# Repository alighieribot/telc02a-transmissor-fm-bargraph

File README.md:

# Sistema de Transmissao FM VHF, Recepcao SDR e Indicador de Nivel Bargraph — TELC02A UNIFEI

Repositorio de engenharia, automacao de projeto eletronico, memorial de calculos e documentacao de bancada do sistema de transmissao em frequencia modulada e monitoramento visual de envolvente de audio desenvolvido para a disciplina **TELC02A — Telecomunicacoes II** da **Universidade Federal de Itajuba**.

---

## Identificacao Academica

| Campo | Informacao |
|---|---|
| **Instituicao** | Universidade Federal de Itajuba — UNIFEI |
| **Disciplina** | TELC02A — Telecomunicacoes II |
| **Docentes Responsaveis** | Prof. Dr. Danilo Henrique Spadoti e Prof. Dr. Mateus Augusto Faustino Chaib Junqueira |
| **Docentes e Tecnicos Colaboradores** | Prof. Dr. Decio Renno de Mendonca, Prof. Dr. Luciano Bertini e Tecnico Anderson — LPCI e LabTel |
| **Integrante 1** | Leonardo Mendonca Costa — Matricula 2024001025 |
| **Integrante 2** | Matheus Martins Venga — Matricula 2024005285 |
| **Integrante 3** | Pedro Henrique Dos Santos Barbosa — Matricula 2022013760 |
| **Integrante 4** | Pedro Henrique Oliveira Francisco — Matricula 2022003245 |
| **Relatorio Entregue** | [Relatorio Telecomunicacoes II.pdf](Relat%C3%B3rio%20Telecomunica%C3%A7%C3%B5es%20II.pdf) |

---

## Sumario

1. [Arquitetura do Sistema e Fluxo de Sinal](#1-arquitetura-do-sistema-e-fluxo-de-sinal)
2. [Fundamentacao Teorica](#2-fundamentacao-teorica)
3. [Adaptacoes de Topologia e Projeto de Esquematicos no KiCad 9.0](#3-adaptacoes-de-topologia-e-projeto-de-esquematicos-no-kicad-90)
4. [Especificacoes e Lista de Materiais](#4-especificacoes-e-lista-de-materiais)
5. [Memorial de Calculos de Engenharia](#5-memorial-de-calculos-de-engenharia)
6. [Projeto de Layout da PCB, Geometria Trapezoidal e Validacao ERC/DRC](#6-projeto-de-layout-da-pcb-geometria-trapezoidal-e-validacao-ercdrc)
7. [Processo de Fabricacao Fisica, Corrosao e Montagem das Placas](#7-processo-de-fabricacao-fisica-corrosao-e-montagem-das-placas)
8. [Ensaios de Bancada, Diagnostico de Falhas e Instrumentacao RF](#8-ensaios-de-bancada-diagnostico-de-falhas-e-instrumentacao-rf)
9. [Localizacao Diferencial da Portadora e Demodulacao WFM via RTL-SDR e SDR# Studio](#9-localizacao-diferencial-da-portadora-e-demodulacao-wfm-via-rtl-sdr-e-sdr-studio)
10. [Estrutura do Repositorio e Automacao via Scripts e Testes](#10-estrutura-do-repositorio-e-automacao-via-scripts-e-testes)
11. [Referencias Tecnicas](#11-referencias-tecnicas)

---

## 1. Arquitetura do Sistema e Fluxo de Sinal

O projeto compreende uma cadeia completa de comunicacao analogica em VHF dividida em tres subsistemas interconectados:

1. **Subsistema A — Transmissor FM VHF (`kicad/transmissor/`):** Oscilador Colpitts de estagio unico em configuracao de base comum alimentado por celula de ions de litio 18650 de $3{,}7\ \text{V}$ a $4{,}2\ \text{V}$, com atenuador resistivo de entrada P2 para nivel de linha e antena monopolo vertical acoplada diretamente ao tanque LC de coletor.
2. **Subsistema de Recepcao e Analise Espectral (`gnuradio/` e `SDR# Studio`):** Receptor de radio definido por software `RTL-SDR` equipado com controlador `RTL2832U` e sintonizador `Fitipower FC0012`, responsavel pela captura em quadratura a $2{,}048\ \text{MSPS}$, visualizacao do espectro e do espectrograma em cascata e demodulacao FM de banda larga.
3. **Subsistema B — Indicador de Nivel de Audio Bargraph (`kicad/vu_meter/`):** Mostra visual de 10 LEDs em modo barra alimentada em $9\ \text{V}$, projetada originalmente em torno do controlador logaritmico `LM3915N-1` de $3\ \text{dB/degrau}$ e validada experimentalmente tambem com o controlador linear `LM3914N` apos substituicao em bancada.

```mermaid
flowchart LR
    subgraph TX["Subsistema A: Transmissor FM VHF (Placa Corroida 46x30 mm)"]
        A1["Fonte de Audio P2\nCelular / Linha (~0,5 a 1,0 Vp)"] --> A2["Divisor Atenuador 11:1\nR1 = 10 kOhm | R5 = 1 kOhm"]
        A2 --> A3["Acoplamento AC\nC2 = 10 uF / 16 V"]
        A3 --> A4["Oscilador Colpitts Base Comum\nQ1 = PN2222A (substituto do BF494)\nC1 = 47 nF ao GND | C3 = 4,7 pF"]
        A4 --> A5["Tanque Ressonante LC\nL1 = 4 espiras | CV1 = 3-30 pF"]
        A5 --> A6["Antena Monopolo Vertical\nAE1 = 20 a 25 cm fio 20 AWG"]
    end

    subgraph CANAL["Canal Sem Fio VHF (62,810 MHz)"]
        A6 -. "Portadora WFM\nfc = 62,810 MHz\nSNR = +20,5 dB\nBW = 180 a 300 kHz" .-> B1["Antena Receptora\nDongle RTL-SDR"]
    end

    subgraph RX["Subsistema de Recepcao SDR"]
        B1 --> B2["Sintonizador Fitipower FC0012\n+ Demodulador RTL2832U\n2,048 MSPS I/Q | Ganho 7,1 dB"]
        B2 --> B3["SDR# Studio / GNU Radio\nDemodulador WFM Mono\nOffset Tuning Ativo"]
    end

    subgraph VU["Subsistema B: Bargraph VU Meter (Placa Ilhada)"]
        B3 -- "Audio Demodulado\nSaida P2" --> C1["Condicionamento de Entrada\nR2 = 1 kOhm | RP1 = 10 kOhm a 100 kOhm"]
        C1 --> C2["Comparador de 10 Niveis\nLM3915N-1 (3 dB/passo) / LM3914N\nVref = 1,25 V | R1 = 2,2 kOhm"]
        C2 --> C3["Matriz de 10 LEDs em Modo Barra\n4 Verdes | 3 Amarelos | 3 Vermelhos\nI_LED = 5,68 mA | Vcc = 9 V"]
    end
```

---

## 2. Fundamentacao Teorica

### 2.1 Modulacao em Frequencia e Regra de Carson

Na modulacao em frequencia, a frequencia instantanea da portadora varia linearmente em torno da frequencia central $\omega_c = 2\pi f_c$ proporcionalmente ao sinal modulante de mensagem $m(t)$, mantendo o envelope de amplitude $A_c$ constante:

$$s_{\text{FM}}(t) = A_c \cos\left(\omega_c t + k_f \int_{0}^{t} m(\tau)\,d\tau\right)$$

onde $k_f$ representa a sensibilidade em frequencia do modulador. O desvio maximo de frequencia $\Delta f$ em relacao a portadora e expresso por:

$$\Delta f = \frac{1}{2\pi} \max\left|\frac{d\phi(t)}{dt}\right| = \frac{k_f}{2\pi} \max|m(t)|$$

Pela Regra de Carson, a largura de banda de radiofrequencia $B_{\text{FM}}$ que concentra aproximadamente $98\%$ da potencia espectral de uma portadora modulada por um sinal com frequencia maxima $f_m$ e dada por:

$$B_{\text{FM}} = 2(\Delta f + f_m) = 2 f_m (\beta_{\text{FM}} + 1), \quad \beta_{\text{FM}} = \frac{\Delta f}{f_m}$$

### 2.2 Oscilador Colpitts em Base Comum e Modulacao Direta por Capacitancia de Juncao

No oscilador Colpitts de um unico transistor, o capacitor $C_1$ conectado entre a base e a referencia `GND` apresenta reatancia desprezivel na faixa de VHF, aterrando a base para sinais de alta frequencia. O circuito ressonante paralelo no coletor e constituido pelo indutor $L_1$ e pelo capacitor ajustavel $CV_1$. A realimentacao positiva que sustenta a oscilacao segundo o criterio de Barkhausen provem do divisor capacitivo formado por $C_3$ entre coletor e emissor e pela capacitancia interna base-emissor $C_{be}$ do transistor.

Quando o sinal de audio proveniente da entrada P2 e injetado na base por meio do capacitor eletrolitico $C_2$, a tensao coletor-base instantanea $v_{CB}(t)$ sofre variacao na taxa do sinal de audio. Essa variacao altera a largura da regiao de deplecao da juncao coletor-base, modulando sua capacitancia de transicao $C_{ob}(v_{CB})$:

$$C_{ob}(v_{CB}) = \frac{C_{ob0}}{\left(1 + \dfrac{v_{CB}}{\Psi_0}\right)^n}$$

Como $C_{ob}(v_{CB})$ encontra-se diretamente em paralelo com o tanque ressonante $L_1 \parallel CV_1$, a variacao de capacitancia produz o desvio instantaneo da frequencia de oscilacao $f_0(t)$, gerando a onda modulada em frequencia.

### 2.3 Quantizacao por Comparadores em Escada no `LM3915N-1` e `LM3914N`

Os circuitos integrados `LM3915N-1` e `LM3914N` integram uma fonte de tensao de referencia ajustavel de $1{,}25\ \text{V}$, uma cadeia divisora resistiva flutuante e 10 comparadores de tensao com saidas em coletor aberto dotadas de regulacao interna de corrente para acionamento direto de LEDs.

- No **`LM3915N-1`**, a cadeia divisora possui incrementos logaritmicos de $3\ \text{dB}$ entre comparadores adjacentes, cobrindo um intervalo dinamico de $30\ \text{dB}$ adequado a percepcao acustica humana.
- No **`LM3914N`**, utilizado como substituto funcional compativel pino a pino na etapa final de bancada, a cadeia divisora e constituida por 10 resistores iguais de $1\ \text{k}\Omega$, estabelecendo degraus lineares de $125\ \text{mV}$ para fundo de escala de $1{,}25\ \text{V}$.
- O pino 9 seleciona o modo de exibicao: quando conectado a $+V_{CC}$, habilita o modo barra, mantendo acesos todos os LEDs cujo limiar foi superado pela envolvente do sinal aplicado ao pino 5.

---

## 3. Adaptacoes de Topologia e Projeto de Esquematicos no KiCad 9.0

Os dois circuitos foram modelados no **KiCad 9.0.4** a partir de geradores declarativos em Python ([tools/generate_kicad.py](tools/generate_kicad.py) e [tools/kicad_sheet.py](tools/kicad_sheet.py)) sincronizados com as netlists formais em formato JSON ([netlists/transmissor_te1.json](netlists/transmissor_te1.json) e [netlists/vu_meter_lm3915.json](netlists/vu_meter_lm3915.json)).

### 3.1 Modificacoes Executadas sobre os Circuitos de Referencia

```mermaid
flowchart TD
    subgraph TX_MOD["Adaptacoes no Transmissor FM (Referencia Te1 -> Projeto TELC02A)"]
        T1["Remocao do microfone de eletreto\ne desconexao de R1 do barramento VCC"] --> T2["Insercao de conector P2 femea J1\ne divisor resistivo 11:1 (R1 = 10 kOhm, R5 = 1 kOhm)"]
        T2 --> T3["Conexao direta de C1 (47 nF)\nda Base de Q1 para a malha GND"]
        T3 --> T4["Substituicao do BF494 defeituoso pelo PN2222A\ncom adequacao da pinagem E-B-C para C-E-B"]
        T4 --> T5["Alimentacao por celula Li-Ion 18650 (3,7 a 4,2 V)\ne antena monopolo vertical de 20 a 25 cm"]
    end

    subgraph VU_MOD["Adaptacoes no Bargraph VU Meter (Referencia Ibytes -> Projeto TELC02A)"]
        V1["Reducao da tensao de alimentacao\nde 12 V para 9 V"] --> V2["Dimensionamento de R1 = 2,2 kOhm\npara limitar I_LED em 5,68 mA e P_D em 0,40 W"]
        V2 --> V3["Remocao do resistor redundante R3\nque curto-circuitava dois nos de GND no esquema original"]
        V3 --> V4["Reducao do resistor serie de entrada R2\nde 10 kOhm para 1 kOhm para ganho de sensibilidade"]
        V4 --> V5["Montagem em soquete DIP-18 permitindo\nsubstituicao imediata do LM3915N-1 pelo LM3914N"]
    end
```

### 3.2 Esquematico do Transmissor FM VHF (`kicad/transmissor/transmissor_te1.kicad_sch`)

### 3.3 Esquematico do Bargraph VU Meter (`kicad/vu_meter/vu_meter_lm3915.kicad_sch`)

---

## 4. Especificacoes e Lista de Materiais

### 4.1 Parametros Operacionais Consolidados

| Subsistema | Parametro | Especificacao de Projeto e Medicao |
|---|---|---|
| **Transmissor FM** | Elemento ativo `Q1` | Transistor NPN `PN2222A` ($f_T = 300\ \text{MHz}$, substituto do `BF494`) |
| **Transmissor FM** | Alimentacao `BT1` | Celula Li-Ion 18650 de $3{,}7\ \text{V}$ a $4{,}2\ \text{V}$ (ensaiado em fonte ate $12\ \text{V}$) |
| **Transmissor FM** | Indutor do tanque `L1` | 4 espiras de fio de cobre esmaltado de $0{,}81\ \text{mm}$ a $1{,}0\ \text{mm}$, nucleo de ar, forma de $7\ \text{mm}$ |
| **Transmissor FM** | Capacitor de sintonia `CV1` | Trimmer ajustavel de $3\ \text{pF}$ a $30\ \text{pF}$ |
| **Transmissor FM** | Capacitor de realimentacao `C3` | Ceramico disco de $4{,}7\ \text{pF}$ (codigo EIA `479`) |
| **Transmissor FM** | Entrada de audio `J1` | Conector P2 femea com divisor atenuador $11:1$ ($-20{,}83\ \text{dB}$) |
| **Transmissor FM** | Antena `AE1` | Monopolo vertical de fio de cobre esmaltado de $20\ \text{cm}$ a $25\ \text{cm}$ |
| **Transmissor FM** | Frequencia da portadora medida | $62{,}810\ \text{MHz}$ em pausa; desvio sob modulacao entre $62{,}750\ \text{MHz}$ e $62{,}810\ \text{MHz}$ |
| **Receptor SDR** | Hardware receptor | Dongle USB `RTL-SDR` (`RTL2832U` + sintonizador `Fitipower FC0012`) |
| **Receptor SDR** | Configuracao no `SDR# Studio` | Modo `WFM` mono, filtro de $180\ \text{kHz}$ a $340\ \text{kHz}$, $2{,}048\ \text{MSPS}$, `Offset Tuning` ativo, ganho de $7{,}1\ \text{dB}$ |
| **Bargraph VU** | Circuito integrado `CI1` | `LM3915N-1` (escala logaritmica de $3\ \text{dB/passo}$) / `LM3914N` (escala linear) em soquete DIP-18 |
| **Bargraph VU** | Alimentacao e Modo | $9\ \text{V}$ DC (conector J4 / bateria) em modo barra (pino 9 em $+9\ \text{V}$) |
| **Bargraph VU** | Indicadores luminosos | 10 LEDs difusos de $5\ \text{mm}$: 4 verdes, 3 amarelos e 3 vermelhos ($I_{\text{LED}} = 5{,}68\ \text{mA}$) |

### 4.2 Lista de Materiais — Circuito A: Transmissor FM VHF

| Designador | Componente | Valor / Especificacao | Footprint KiCad | Funcao no Circuito |
|---|---|---|---|---|
| `Q1` | Transistor NPN | `PN2222A` / `BF494` (TO-92) | `Package_TO_SOT_THT:TO-92_Inline_Wide` | Oscilador Colpitts em base comum e modulador FM |
| `J1` | Conector P2 femea | $3{,}5\ \text{mm}$ stereo/mono | `Connector_PinHeader_2.54mm:PinHeader_1x02_P2.54mm_Vertical` | Entrada de sinal de audio em nivel de linha |
| `R1` | Resistor filme de carbono | $10\ \text{k}\Omega$, $1/4\ \text{W}$, $5\%$ | `Resistor_THT:R_Axial_DIN0207_L6.3mm_D2.5mm_P10.16mm_Horizontal` | Ramo serie do atenuador de entrada |
| `R5` | Resistor filme de carbono | $1\ \text{k}\Omega$, $1/4\ \text{W}$, $5\%$ | `Resistor_THT:R_Axial_DIN0207_L6.3mm_D2.5mm_P10.16mm_Horizontal` | Ramo shunt para `GND` do atenuador de entrada |
| `R2` | Resistor filme de carbono | $8{,}2\ \text{k}\Omega$, $1/4\ \text{W}$, $5\%$ | `Resistor_THT:R_Axial_DIN0207_L6.3mm_D2.5mm_P10.16mm_Horizontal` | Polarizacao superior da base (`VCC` para `BASE`) |
| `R3` | Resistor filme de carbono | $5{,}6\ \text{k}\Omega$, $1/4\ \text{W}$, $5\%$ | `Resistor_THT:R_Axial_DIN0207_L6.3mm_D2.5mm_P10.16mm_Horizontal` | Polarizacao inferior da base (`BASE` para `GND`) |
| `R4` | Resistor filme de carbono | $47\ \Omega$, $1/4\ \text{W}$, $5\%$ | `Resistor_THT:R_Axial_DIN0207_L6.3mm_D2.5mm_P10.16mm_Horizontal` | Degeneracao e estabilizacao DC de emissor |
| `C1` | Capacitor ceramico disco | $47\ \text{nF}$ (codigo `473`) | `Capacitor_THT:C_Disc_D5.0mm_W2.5mm_P5.00mm` | Desacoplamento de RF da base para `GND` |
| `C2` | Capacitor eletrolitico radial | $10\ \mu\text{F} / 16\ \text{V}$ | `Capacitor_THT:CP_Radial_D5.0mm_P2.00mm` | Bloqueio DC e acoplamento de audio para a base |
| `C3` | Capacitor ceramico disco | $4{,}7\ \text{pF}$ (codigo `479`) | `Capacitor_THT:C_Disc_D5.0mm_W2.5mm_P5.00mm` | Realimentacao positiva coletor-emissor |
| `C4` | Capacitor ceramico disco | $100\ \text{nF}$ (codigo `104`) | `Capacitor_THT:C_Disc_D5.0mm_W2.5mm_P5.00mm` | Desacoplamento de alta frequencia da bateria |
| `CV1` | Capacitor trimmer | $3\ \text{pF}$ a $30\ \text{pF}$ | `Capacitor_THT:C_Disc_D5.0mm_W2.5mm_P5.00mm` | Ajuste da frequencia de ressonancia do coletor |
| `L1` | Indutor solenoide ar | 4 espiras fio 20 AWG em $7\ \text{mm}$ | `Inductor_THT:L_Axial_L5.3mm_D2.2mm_P7.62mm_Horizontal_Vishay_IM-1` | Indutancia do circuito tanque ressonante |
| `AE1` | Antena monopolo | $20\ \text{cm}$ a $25\ \text{cm}$ fio esmaltado | `Connector_PinHeader_2.54mm:PinHeader_1x01_P2.54mm_Vertical` | Irradiacao eletromagnetica em VHF |
| `BT1` | Suporte e celula 18650 | Li-Ion $3{,}7\ \text{V}$ a $4{,}2\ \text{V}$ | `Connector_PinHeader_2.54mm:PinHeader_1x02_P2.54mm_Vertical` | Alimentacao DC do transmissor |

### 4.3 Lista de Materiais — Circuito B: Bargraph VU Meter

| Designador | Componente | Valor / Especificacao | Funcao no Circuito |
|---|---|---|---|
| `CI1` | Circuito integrado + soquete | `LM3915N-1` / `LM3914N` (DIP-18) | Driver de 10 comparadores com fonte de referencia de $1{,}25\ \text{V}$ |
| `D1` a `D4` | 4 LEDs difusos $5\ \text{mm}$ | Cor verde ($V_F \approx 2{,}0\ \text{V}$) | Indicacao dos 4 primeiros niveis de sinal |
| `D5` a `D7` | 3 LEDs difusos $5\ \text{mm}$ | Cor amarela ($V_F \approx 2{,}0\ \text{V}$) | Indicacao da faixa intermediaria de transicao |
| `D8` a `D10` | 3 LEDs difusos $5\ \text{mm}$ | Cor vermelha ($V_F \approx 1{,}9\ \text{V}$) | Indicacao de topo de escala |
| `R1` | Resistor filme de carbono | $2{,}2\ \text{k}\Omega$, $1/4\ \text{W}$, $5\%$ | Programacao da corrente de saida dos LEDs em $5{,}68\ \text{mA}$ |
| `R2` | Resistor filme de carbono | $1\ \text{k}\Omega$ (substituiu o de $10\ \text{k}\Omega$ inicial) | Limitacao de corrente em serie com a entrada P2 |
| `RP1` | Potenciometro rotativo linear | $100\ \text{k}\Omega$ (`B100K`) / $10\ \text{k}\Omega$ | Divisor ajustavel de sensibilidade para o pino 5 |
| `C2` | Capacitor ceramico disco | $100\ \text{nF}$ (codigo `104`) | Desacoplamento local junto aos pinos 2 e 3 do CI |
| `C5` | Capacitor eletrolitico radial | $100\ \mu\text{F} / 16\ \text{V}$ | Filtragem de baixa frequencia da fonte de $9\ \text{V}$ |
| `J1` | Conector P2 femea | $3{,}5\ \text{mm}$ | Entrada do sinal de audio demodulado |
| `BT1` | Conector Jack DC J4 + Fonte/Bateria | $9{,}0\ \text{V}$ DC | Alimentacao principal do circuito bargraph |

---

## 5. Memorial de Calculos de Engenharia

### 5.1 Estagio de Entrada de Audio do Transmissor (`R1`, `R5` e `C2`)

O divisor resistivo formado por $R_1 = 10\ \text{k}\Omega$ e $R_5 = 1\ \text{k}\Omega$ reduz a amplitude de linha proveniente do celular para a faixa linear de modulacao da base:

$$A_v = \frac{R_5}{R_1 + R_5} = \frac{1000}{10000 + 1000} = \frac{1}{11} \approx 0{,}0909 \quad (-20{,}83\ \text{dB})$$

Para uma tensao de entrada $V_{\text{in}} = 0{,}50\ \text{V}_{\text{pico}}$, a tensao AC entregue ao capacitor de acoplamento $C_2 = 10\ \mu\text{F}$ e $V_{\text{base(AC)}} \approx 45{,}5\ \text{mV}_{\text{pico}}$. A resistencia equivalente vista por $C_2$ combina $R_1 \parallel R_5 = 909{,}1\ \Omega$ em serie com $R_2 \parallel R_3 = 8{,}2\ \text{k}\Omega \parallel 5{,}6\ \text{k}\Omega = 3327{,}5\ \Omega$:

$$R_{\text{eq(AC)}} = 909{,}1 + 3327{,}5 = 4236{,}6\ \Omega \implies f_{c(\text{inf})} = \frac{1}{2\pi \cdot R_{\text{eq(AC)}} \cdot C_2} = \frac{1}{2\pi \times 4236{,}6 \times 10 \times 10^{-6}} \approx 3{,}76\ \text{Hz}$$

### 5.2 Polarizacao Quiescente DC do Transistor `PN2222A` (`V_CC = 4,0 V`)

Com a celula Li-Ion 18650 operando em $V_{CC} = 4{,}0\ \text{V}$:

$$V_{TH} = V_{CC} \cdot \frac{R_3}{R_2 + R_3} = 4{,}0 \times \frac{5600}{8200 + 5600} \approx 1{,}623\ \text{V}, \quad R_{TH} = \frac{8200 \times 5600}{13800} \approx 3327{,}5\ \Omega$$

Adotando $V_{BE} = 0{,}70\ \text{V}$, $\beta = 150$ e $R_4 = 47\ \Omega$:

$$I_{EQ} = \frac{V_{TH} - V_{BE}}{R_4 + \dfrac{R_{TH}}{\beta + 1}} = \frac{1{,}623 - 0{,}70}{47 + \dfrac{3327{,}5}{151}} = \frac{0{,}923}{69{,}04} \approx 13{,}37\ \text{mA}, \quad I_{CQ} \approx 13{,}28\ \text{mA}$$

$$V_E = I_{EQ} \cdot R_4 \approx 0{,}628\ \text{V}, \quad V_B = V_E + V_{BE} \approx 1{,}328\ \text{V}, \quad V_{CEQ} = V_{CC} - V_E \approx 3{,}372\ \text{V}$$

$$P_{D(\text{Q1})} = V_{CEQ} \cdot I_{CQ} = 3{,}372\ \text{V} \times 13{,}28\ \text{mA} \approx 44{,}8\ \text{mW} \ll 625\ \text{mW}, \quad g_m = \frac{I_{CQ}}{V_T} \approx 0{,}511\ \text{S}$$

### 5.3 Reatancia de Aterramento de RF da Base (`C1 = 47 nF`)

Na frequencia medida da portadora ($f_0 = 62{,}810\ \text{MHz}$), o capacitor $C_1 = 47\ \text{nF}$ entre a base e o `GND` apresenta reatancia:

$$X_{C1(\text{RF})} = \frac{1}{2\pi \cdot f_0 \cdot C_1} = \frac{1}{2\pi \times 62{,}81 \times 10^6 \times 47 \times 10^{-9}} \approx 0{,}054\ \Omega$$

garantindo o aterramento de RF da base para a topologia em base comum.

### 5.4 Indutancia `L1` (Wheeler) e Frequencia da Portadora com `PN2222A` (`62,810 MHz`)

Para o solenoide de camada unica com nucleo de ar de $N = 4$ espiras:
- **Geometria nominal sobre forma de $7{,}0\ \text{mm}$ ($d = 0{,}3075\ \text{pol}$, $l = 0{,}1378\ \text{pol}$):**
  $$L_{1(\text{nom})} = \frac{N^2 \cdot d^2}{18d + 40l} = \frac{16 \times (0{,}3075)^2}{18(0{,}3075) + 40(0{,}1378)} \approx 0{,}137\ \mu\text{H}$$
- **Geometria fisica na placa apos relaxacao mecanica da espira ($D_{\text{ef}} \approx 9{,}0\ \text{mm} = 0{,}354\ \text{pol}$, $l \approx 4{,}5\ \text{mm} = 0{,}177\ \text{pol}$) somada a indutancia parasita dos terminais ($L_{\text{par}} \approx 25\ \text{nH}$):**
  $$L_{\text{bobina}} = \frac{16 \times (0{,}354)^2}{18(0{,}354) + 40(0{,}177)} \approx 0{,}149\ \mu\text{H} \implies L_{\text{total}} = 0{,}149 + 0{,}025 = 0{,}174\ \mu\text{H}$$

A capacitancia equivalente paralela total no no do coletor ($C_{\text{total}}$) com o transistor `PN2222A` ($C_{ib} \approx 25\ \text{pF}$, $C_{ob} \approx 8{,}0\ \text{pF}$) soma:
1. **Malha de realimentacao ($C_3 = 4{,}7\ \text{pF}$ em serie com $C_{ib} = 25\ \text{pF}$):** $C_{\text{eq}} = \dfrac{4{,}7 \times 25}{4{,}7 + 25} \approx 3{,}96\ \text{pF}$
2. **Capacitancia de saida coletor-base do `PN2222A`:** $C_{ob} \approx 8{,}0\ \text{pF}$
3. **Capacitancia equivalente da antena monopolo curta (`AE1`):** $C_{\text{ant}} \approx 1{,}73\ \text{pF}$
4. **Trimmer `CV1` (`3 a 30 pF`) ajustado em $C_{V1} \approx 23{,}2\ \text{pF}$:**
   $$C_{\text{total}} = 23{,}2 + 3{,}96 + 8{,}0 + 1{,}73 = 36{,}89\ \text{pF}$$

Aplicando a formula de Thomson:

$$f_0 = \frac{1}{2\pi \sqrt{L_{\text{total}} \cdot C_{\text{total}}}} = \frac{1}{2\pi \sqrt{0{,}174 \times 10^{-6} \times 36{,}89 \times 10^{-12}}} \approx 62{,}81\ \text{MHz}$$

### 5.5 Dimensionamento Termico e Limiares do Bargraph (`LM3915N-1` e `LM3914N`)

Com os pinos 6 e 7 interligados, pino 8 em `GND` e resistor $R_1 = 2{,}2\ \text{k}\Omega$ para `GND`:

$$V_{\text{REF}} = 1{,}25\ \text{V}, \quad I_{\text{REF}} = \frac{1{,}25\ \text{V}}{2200\ \Omega} \approx 0{,}568\ \text{mA}, \quad I_{\text{LED}} \approx \frac{12{,}5\ \text{V}}{R_1} \approx 5{,}68\ \text{mA/LED}$$

Em modo barra com $V_{CC} = 9{,}0\ \text{V}$ e $V_{\text{LED}} \approx 2{,}0\ \text{V}$, a dissipacao maxima com os 10 LEDs acesos simultaneamente e:

$$P_{D(\text{max})} = 10 \cdot (V_{CC} - V_{\text{LED}}) \cdot I_{\text{LED}} = 10 \times (9{,}0 - 2{,}0) \times 0{,}00568 \approx 0{,}398\ \text{W} < 1{,}365\ \text{W (limite do DIP-18)}$$

A tabela a seguir compara os 10 limiares de acionamento no pino 5 ($V_{\text{SIG}}$) entre o controlador logaritmico original (`LM3915N-1`, passo de $-3\ \text{dB}$) e o controlador linear instalado apos a substituicao em bancada (`LM3914N`, passo de $125\ \text{mV}$):

| LED | Pino DIP-18 | Cor | Nivel `LM3915N-1` (Log) | Limiar $V_{\text{SIG}}$ no `LM3915N-1` | Proporcao `LM3914N` (Linear) | Limiar $V_{\text{SIG}}$ no `LM3914N` |
|---|---|---|---|---|---|---|
| `D1` | Pino 1 | Verde | $-27\ \text{dB}$ | $0{,}0558\ \text{V}$ ($55{,}8\ \text{mV}$) | $10\%$ | $0{,}1250\ \text{V}$ ($125{,}0\ \text{mV}$) |
| `D2` | Pino 18 | Verde | $-24\ \text{dB}$ | $0{,}0789\ \text{V}$ ($78{,}9\ \text{mV}$) | $20\%$ | $0{,}2500\ \text{V}$ ($250{,}0\ \text{mV}$) |
| `D3` | Pino 17 | Verde | $-21\ \text{dB}$ | $0{,}1114\ \text{V}$ ($111{,}4\ \text{mV}$) | $30\%$ | $0{,}3750\ \text{V}$ ($375{,}0\ \text{mV}$) |
| `D4` | Pino 16 | Verde | $-18\ \text{dB}$ | $0{,}1574\ \text{V}$ ($157{,}4\ \text{mV}$) | $40\%$ | $0{,}5000\ \text{V}$ ($500{,}0\ \text{mV}$) |
| `D5` | Pino 15 | Amarelo | $-15\ \text{dB}$ | $0{,}2223\ \text{V}$ ($222{,}3\ \text{mV}$) | $50\%$ | $0{,}6250\ \text{V}$ ($625{,}0\ \text{mV}$) |
| `D6` | Pino 14 | Amarelo | $-12\ \text{dB}$ | $0{,}3140\ \text{V}$ ($314{,}0\ \text{mV}$) | $60\%$ | $0{,}7500\ \text{V}$ ($750{,}0\ \text{mV}$) |
| `D7` | Pino 13 | Amarelo | $-9\ \text{dB}$ | $0{,}4435\ \text{V}$ ($443{,}5\ \text{mV}$) | $70\%$ | $0{,}8750\ \text{V}$ ($875{,}0\ \text{mV}$) |
| `D8` | Pino 12 | Vermelho | $-6\ \text{dB}$ | $0{,}6265\ \text{V}$ ($626{,}5\ \text{mV}$) | $80\%$ | $1{,}0000\ \text{V}$ ($1000{,}0\ \text{mV}$) |
| `D9` | Pino 11 | Vermelho | $-3\ \text{dB}$ | $0{,}8849\ \text{V}$ ($884{,}9\ \text{mV}$) | $90\%$ | $1{,}1250\ \text{V}$ ($1125{,}0\ \text{mV}$) |
| `D10` | Pino 10 | Vermelho | $0\ \text{dB}$ | $1{,}2500\ \text{V}$ ($1250{,}0\ \text{mV}$) | $100\%$ | $1{,}2500\ \text{V}$ ($1250{,}0\ \text{mV}$) |

---

## 6. Projeto de Layout da PCB, Geometria Trapezoidal e Validacao ERC/DRC

O layout da placa do transmissor ([kicad/transmissor/transmissor_te1.kicad_pcb](kicad/transmissor/transmissor_te1.kicad_pcb)) foi sintetizado programaticamente via API `pcbnew` do KiCad 9.0 ([tools/generate_pcb.py](tools/generate_pcb.py)) obedecendo aos seguintes criterios de compatibilidade eletromagnetica e manufaturabilidade por corrosao quimica:

1. **Dimensoes e Camada:** Placa de face simples na camada inferior de cobre (`B.Cu`) com contorno externo `Edge.Cuts` de exatamente $46{,}0 \times 30{,}0\ \text{mm}$.
2. **Geometria Trapezoidal a 45/135 Graus (Zero Angulos Retos):** Todas as mudancas de direcao e derivacoes em Y foram roteadas exclusivamente com segmentos ortogonais e chanfros a $45^\circ$ e $135^\circ$. A ausencia de cantos de $90^\circ$ evita concentracao de acido durante a corrosao e reduz descontinuidades de impedancia em VHF. Essa propriedade e verificada matematicamente pelo teste automatizado `test_transmitter_pcb_tracks_are_trapezoidal_without_right_angles` em [tests/test_kicad.py](tests/test_kicad.py).
3. **Plano de Terra e Larguras de Trilha:** Toda a area livre da camada `B.Cu` foi preenchida por uma zona de cobre conectada a malha `GND` com folga de isolamento (`clearance`) de $0{,}50\ \text{mm}$ e alivio termico nos pads aterrados. As trilhas foram dimensionadas em $1{,}2\ \text{mm}$ para `VCC`, $1{,}0\ \text{mm}$ para o tanque de RF do coletor e $0{,}8\ \text{mm}$ para polarizacao e audio.

| Renderizacao 3D — Face Superior dos Componentes | Renderizacao 3D — Face Inferior de Cobre (`B.Cu`) |
|---|---|
|  |  |

| Verificacao de Regras Eletricas (ERC — 0 Violacoes) | Verificacao de Regras de Layout (DRC — 0 Violacoes) |
|---|---|
|  |  |

---

## 7. Processo de Fabricacao Fisica, Corrosao e Montagem das Placas

### 7.1 Fotolito Replicado 4x4 em Escala 1:1 e Corrosao da PCB do Transmissor

Para garantir repetibilidade no processo de transferencia termica de toner, o script [tools/generate_pcb.py](tools/generate_pcb.py) gera automaticamente o arquivo [kicad/transmissor/transmissor_te1_toner_transfer.pdf](kicad/transmissor/transmissor_te1_toner_transfer.pdf) contendo uma matriz de $4 \times 4$ copias (16 unidades em escala exata $1:1$ de $46{,}0 \times 30{,}0\ \text{mm}$, espacadas por $12{,}0\ \text{mm}$) em uma unica folha A4 paisagem. A palavra vazada `TELC02A` aparece espelhada no papel impresso (`A20CLET`) e torna-se legivel da esquerda para a direita no cobre apos a transferencia termica.

O procedimento de fabricacao do transmissor compreendeu:
1. Impressao a laser em escala $100\%$ sobre papel fotografico e corte da placa de fenolite cobreada de face simples.
2. Desoxidacao mecanica do cobre com la de aco fina e limpeza com alcool isopropilico.
3. Transferencia termica da mascara de toner com ferro de passar aquecido, seguida de imersao em agua para remocao das fibras de papel e retoque de falhas com caneta permanente preta.
4. Corrosao quimica em solucao de percloreto de ferro realizada em ambiente externo ao predio academico devido as restricoes de uso de reagentes corrosivos nos laboratorios internos.
5. Remocao do toner com solvente, furacao com broca de $1{,}0\ \text{mm}$ e soldagem dos componentes diretamente sobre a face cobreada para minimizar a indutancia parasita dos terminais em VHF, contando com o auxilio do tecnico Anderson no LPCI para a fixacao do suporte da celula 18650 e do conector P2.

| Placa do Transmissor FM Montada — Perspectiva Geral | Detalhe do Tanque LC (`L1`, `CV1`, `Q1`, `C3` e `C1` ao `GND`) | Vista Superior Completa do Transmissor |
|---|---|---|
|  |  |  |

### 7.2 Montagem do Circuito Bargraph em Placa Perfurada Ilhada

O circuito indicador de nivel foi montado sobre uma placa de fenolite perfurada ilhada utilizando um soquete DIP-18 centralizado no lado cobreado, permitindo a substituicao do circuito integrado sem dessoldagem. Os 10 LEDs foram alinhados na borda superior com barramento comum de anodos conectado a $+9\ \text{V}$, enquanto os catodos foram roteados ponto a ponto aos pinos `1` e `18` a `10` do soquete.

| Placa Ilhada do Bargraph — Vista Superior dos Componentes | Face Inferior de Solda (Soquete DIP-18 Inicial) | Face Inferior com `LM3914N` Instalado no Soquete |
|---|---|---|
|  |  |  |

---

## 8. Ensaios de Bancada, Diagnostico de Falhas e Instrumentacao RF

### 8.1 Ensaios e Substituicao de Componentes no Bargraph VU Meter

1. **Ajuste de Ganho de Entrada (`R2`):** Nos ensaios iniciais do bargraph com fonte de bancada regulada em $9\ \text{V}$ e bateria de $9\ \text{V}$ com sinal de audio injetado via cabo P2, constatou-se que o resistor serie de entrada de $10\ \text{k}\Omega$ atenuava excessivamente o sinal antes do potenciometro de $100\ \text{k}\Omega$. A substituicao de $R_2$ por $1\ \text{k}\Omega$ elevou a fracao de tensao entregue ao cursor para $99\%$ com potenciometro de $100\ \text{k}\Omega$ e $90{,}9\%$ com potenciometro de $10\ \text{k}\Omega$, restabelecendo o acionamento de toda a escala luminosa.
2. **Substituicao do `LM3915N-1` pelo `LM3914N`:** Durante a intervencao na bancada para troca do potenciometro por uma unidade de menor resistencia, o exemplar do `LM3915N-1` sofreu avaria eletrica e deixou de responder ao sinal de audio no pino 5. Gracas a presenca do soquete DIP-18 na placa ilhada, o componente foi substituido imediatamente por um exemplar do `LM3914N` cedido pelo Prof. Dr. Luciano Bertini, mantendo a mesma pinagem e corrente de LED ($5{,}68\ \text{mA}$) com resposta em escala linear.

### 8.2 Diagnostico do Lote de Transistores `BF494` e Substituicao pelo `PN2222A`

Na primeira etapa de validacao de RF no Laboratorio de Telecomunicacoes (LabTel), sob orientacao do Prof. Dr. Decio Renno de Mendonca e com o uso do analisador de espectro **Rohde & Schwarz Spectrum Rider FPH**, verificou-se ausencia de portadora na faixa de $88\ \text{MHz}$ a $108\ \text{MHz}$. A inspecao em bancada com o auxilio dos tecnicos do laboratorio comprovou que o lote adquirido de transistores `BF494` encontrava-se defeituoso.

O `BF494` foi substituido pelo transistor NPN `PN2222A` ($f_T = 300\ \text{MHz}$), adequando-se a disposicao dos terminais Emissor-Base-Coletor do `PN2222A` para coincidir com as ilhas Coletor-Emissor-Base da placa.

### 8.3 Ensaios Preliminares de Recepcao com GNU Radio

Para rastrear a nova frequencia de oscilacao do transmissor com o `PN2222A`, desenvolveu-se inicialmente um fluxograma de recepcao `WFM` no **GNU Radio Companion 3.10** ([gnuradio/projeto_telecomdois.grc](gnuradio/projeto_telecomdois.grc)) acoplado ao dongle `RTL-SDR`. Durante os testes em bancada, identificou-se atividade espectral proxima a $61{,}6\ \text{MHz} - 61{,}8\ \text{MHz}$ (deslocada abaixo da faixa comercial de FM pelas capacitancias internas $C_{ob} \approx 8\ \text{pF}$ e $C_{ib} \approx 25\ \text{pF}$ do `PN2222A`), porem a ausencia de espectrograma em cascata (`Waterfall`), o ganho fixo no bloco `Soapy RTLSDR Source` e a falta de filtragem passa-baixas pre-demodulacao limitaram a recuperacao nitida do audio.

| Fluxograma Desenvolvido no GNU Radio (`projeto_telecomdois.grc`) | Ensaio Pratico com RTL-SDR e GNU Radio em `61,63 MHz` |
|---|---|
|  |  |

---

## 9. Localizacao Diferencial da Portadora e Demodulacao WFM via RTL-SDR e SDR# Studio

Para superar as limitacoes do fluxograma inicial no GNU Radio, a recepcao e o diagnostico espectral foram transferidos para o software **SDR# Studio** operando em conjunto com os utilitarios de captura de linha de comando `rtl_power` e `rtl_sdr` sobre o receptor **RTL-SDR (`RTL2832U` + sintonizador `Fitipower FC0012`)**.

### 9.1 Metodo de Subtracao Espectral Diferencial (`ON` vs. `OFF` vs. `PAUSE`)

Realizou-se uma varredura automatizada de $25\ \text{MHz}$ a $115\ \text{MHz}$ seguida de captura de amostras I/Q brutas a $2{,}4\ \text{MSPS}$ com transformada de Fourier de $32768$ pontos e cancelamento matematico de componente DC, comparando o espectro ambiental com a bateria 18650 desconectada (`OFF`) contra o espectro com a placa energizada e o audio do celular em pausa (`PAUSE`):

```text
Frequencia Medida | Diferenca (PAUSE - OFF) | Potencia em PAUSE | Piso sem Bateria (OFF) | Diagnostico
------------------+-------------------------+-------------------+------------------------+----------------------------------
   62,81000 MHz   |       +20,28 dB         |     -21,5 dBFS    |       -42,0 dBFS       | Portadora fundamental do TX FM
   62,75000 MHz   |       +15,10 dB         |     -26,9 dBFS    |       -42,0 dBFS       | Centro de desvio sob modulacao WFM
   62,00000 MHz   |        +0,05 dB         |     -25,0 dBFS    |       -25,0 dBFS       | Harmonico de clock USB (descartado)
```

### 9.2 Parametros Otimizados no `SDR# Studio` e Validacao com Musica

1. **Demodulador e Largura de Banda:** Modo `WFM` mono (`FM Stereo` e `Squelch` desativados), com largura de banda de filtro ajustada entre $180\ \text{kHz}$ e $340\ \text{kHz}$ para abranger integralmente o desvio de frequencia da portadora sem cortar os picos dinamicos de grave.
2. **Controle de Ganho e Conversor A/D:** Taxa de amostragem de $2{,}048\ \text{MSPS}$ em quadratura, `Offset Tuning` ativado para eliminar o corte do filtro DC central do sintonizador `Fitipower FC0012`, controles automaticos `RTL AGC` e `Tuner AGC` **desativados** para impedir a saturacao por campo proximo e ganho manual de RF fixado no degrau de **$7{,}1\ \text{dB}$**.
3. **Analise da Portadora em Pausa vs. Modulacao Musical:**
   - Com a reproducao do celular em **pausa**, observa-se a portadora nao modulada concentrada em **$62{,}810\ \text{MHz}$** com relacao sinal-ruido de **$+20{,}5\ \text{dB}$** acima do piso de $-42\ \text{dBFS}$ e rastro vertical estreito no espectrograma.
   - Ao iniciar a **reproducao musical** via cabo P2, observa-se a abertura simetrica das bandas laterais de modulacao em frequencia ocupando cerca de $180\ \text{kHz}$ a $300\ \text{kHz}$ entre **$62{,}750\ \text{MHz}$ e $62{,}810\ \text{MHz}$**, acompanhando a envolvente ritmica da musica e entregando o audio demodulado na saida do receptor.

| Portadora em Pausa (`62,810 MHz`, `SNR = +20,5 dB`) | Portadora Modulada com Musica via Entrada P2 (`62,750 - 62,810 MHz`) |
|---|---|
|  |  |

---

## 10. Estrutura do Repositorio e Automacao via Scripts e Testes

```text
prj/
├── README.md                                           Documentacao geral, memorial de calculos e resultados de bancada
├── Relatorio Telecomunicacoes II.pdf                   Relatorio tecnico final entregue na disciplina TELC02A
├── .gitignore                                          Filtro de arquivos temporarios do KiCad e Python
├── kicad/
│   ├── transmissor/
│   │   ├── transmissor_te1.kicad_pro                   Projeto KiCad 9.0 do Transmissor FM VHF
│   │   ├── transmissor_te1.kicad_sch                   Esquematico do Transmissor (PN2222A/BF494, Entrada P2, Li-Ion 18650)
│   │   ├── transmissor_te1.kicad_pcb                   Layout da PCB (46,0 x 30,0 mm, face simples B.Cu, trilhas a 45 graus)
│   │   ├── transmissor_te1_toner_transfer.pdf          Folha A4 com matriz 4x4 (16 copias 1:1) para transferencia termica
│   │   ├── transmissor_te1_toner_transfer_mirror.pdf   Folha A4 com matriz 4x4 (16 copias 1:1) espelhada
│   │   ├── transmissor_te1_montagem_top.pdf            Mapa superior de montagem de componentes (F.SilkS + F.Fab)
│   │   └── svg/                                        Esquematico e PCB em SVG + renderizacoes 3D (pcb_top.png, pcb_bottom.png)
│   └── vu_meter/
│       ├── vu_meter_lm3915.kicad_pro                   Projeto KiCad 9.0 do Bargraph VU Meter (LM3915N-1 / LM3914N)
│       ├── vu_meter_lm3915.kicad_sch                   Esquematico do Bargraph (9 V, modo barra, R1 = 2,2 kOhm, R2 = 1 kOhm)
│       └── svg/                                        Esquematico exportado em SVG
├── netlists/
│   ├── transmissor_te1.json                            Netlist declarativa do Transmissor FM
│   └── vu_meter_lm3915.json                            Netlist declarativa do Bargraph VU Meter
├── gnuradio/
│   └── projeto_telecomdois.grc                         Fluxograma do receptor WFM RTL-SDR para GNU Radio Companion 3.10
├── docs/
│   ├── relatorio_transmissor_fm.md                     Texto tecnico detalhado da secao de confeccao e memorial
│   ├── relatorio_figuras/                              Acervo completo de 21 figuras de alta resolucao (KiCad, PCB, fotos, SDR#)
│   ├── datasheets/
│   │   ├── bf494.pdf                                   Datasheet do transistor NPN RF BF494
│   │   └── LM3915N-1.PDF                               Datasheet oficial Texas Instruments LM3915N-1
│   └── referencias/                                    Arquivos originais de referencia (Te1 e Ibytes)
├── tools/
│   ├── generate_kicad.py                               Gerador programatico dos esquematicos KiCad 9.0
│   ├── generate_pcb.py                                 Gerador programatico da PCB e das folhas A4 com 16 copias 1:1
│   ├── kicad_sheet.py                                  Construtor S-expression para folhas de esquematico KiCad 9.0
│   ├── netlist_tools.py                                Funcoes de validacao topologica, divisores e calculos termicos
│   └── trace_copper.py                                 Extrator de conectividade por inundacao de pixels sobre imagem Gerber
└── tests/
    ├── test_kicad.py                                   Testes automatizados de ERC, DRC, paridade, geometria 45 graus e PDFs 1:1
    └── test_projeto.py                                 Testes unitarios de topologia, indutancia Wheeler, corrente e dissipacao
```

### Como Executar a Suite de Verificacao Automatizada (`20/20` Testes)

Com Python 3 e KiCad 9.0 instalados no sistema, execute na raiz do repositorio:

```powershell
python -B -m unittest discover -s tests -v
```

A suite executa `20` verificacoes automatizadas:
- **Validacao KiCad CLI (`tests/test_kicad.py`):** Paridade exata entre as netlists exportadas pelo `kicad-cli` e os arquivos `netlists/*.json`, ausencia de erros de anotacao, **0 violacoes de ERC** nos dois esquematicos, **0 violacoes de DRC e 0 trilhas desconectadas** na PCB do transmissor, **geometria 100% trapezoidal sem angulos retos de 90 graus** em todos os vertices de trilha e verificacao vetorial das **16 copias em escala exata 1:1 ($46{,}00 \times 30{,}00\ \text{mm}$)** nos PDFs de transferencia termica.
- **Validacao Fisico-Matematica (`tests/test_projeto.py`):** Integridade de pinos e redes, divisor atenuador P2 de $11:1$, realimentacao Colpitts entre coletor e emissor, rastreamento por visao computacional das ilhas de cobre, indutancia pela formula de Wheeler, corrente nos LEDs de $5{,}68\ \text{mA}$, dissipacao termica abaixo de $0{,}5\ \text{W}$ em $9\ \text{V}$ e progressao de $3\ \text{dB/passo}$.

---

## 11. Referencias Tecnicas

1. **TEXAS INSTRUMENTS.** *LM3915 Dot/Bar Display Driver Datasheet (SNVS740C)*. Dallas: Texas Instruments, 2000. Disponivel em: [docs/datasheets/LM3915N-1.PDF](docs/datasheets/LM3915N-1.PDF).
2. **PHILIPS SEMICONDUCTORS.** *BF494 NPN Medium Frequency Transistor Product Specification*. Eindhoven: Philips, 1997. Disponivel em: [docs/datasheets/bf494.pdf](docs/datasheets/bf494.pdf).
3. **JUNQUEIRA, Mateus Augusto Faustino Chaib.** *Implementacao da Modulacao em Angulo*. Itajuba: Universidade Federal de Itajuba, 2026. 51 slides. Material de aula da disciplina TELC02A — Telecomunicacoes II.
4. **TONI ELETRONICA.** *Transmissor de FM com BF494 ou BF495: facil montagem*. 2008. Acervo local em: [docs/referencias/te1/](docs/referencias/te1/).
5. **BYTES BRASIL.** *VU Meter LM3915: como montar e projetar a PCB passo a passo*. Acervo local em: [docs/referencias/vu_ibytes/](docs/referencias/vu_ibytes/).

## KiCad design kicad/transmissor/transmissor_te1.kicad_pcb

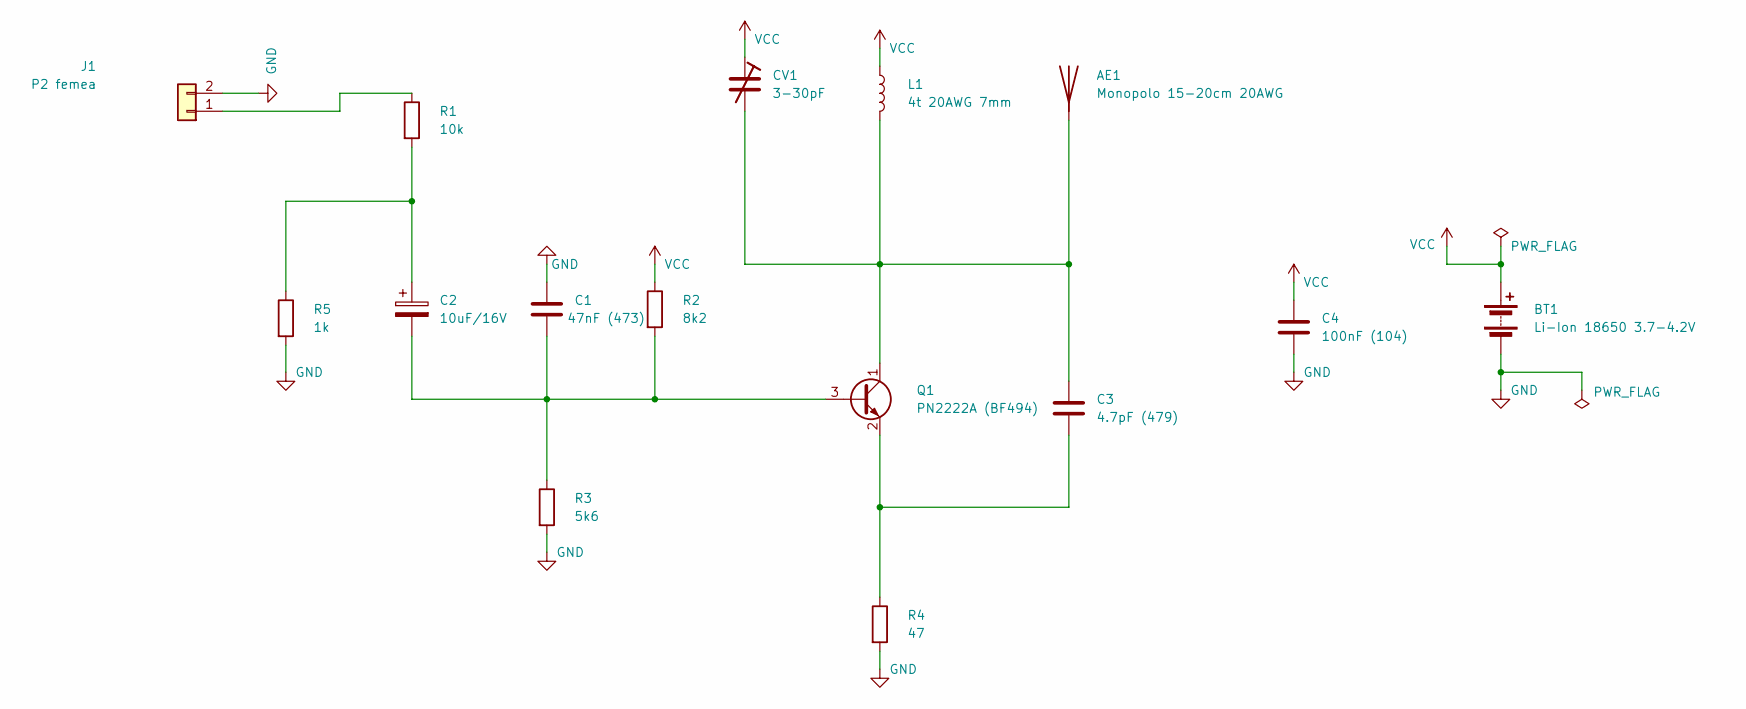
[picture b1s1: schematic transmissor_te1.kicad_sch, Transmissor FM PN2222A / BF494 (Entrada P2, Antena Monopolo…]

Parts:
AE1: Monopolo 15-20cm 20AWG; PinHeader_1x01_P2.54mm_Vertical
BT1: Li-Ion 18650 3.7-4.2V; PinHeader_1x02_P2.54mm_Vertical
C1: 47nF (473); C_Disc_D5.0mm_W2.5mm_P5.00mm
C2: 10uF/16V; CP_Radial_D5.0mm_P2.00mm
C3: 4.7pF (479); C_Disc_D5.0mm_W2.5mm_P5.00mm
C4: 100nF (104); C_Disc_D5.0mm_W2.5mm_P5.00mm
CV1: 3-30pF; C_Disc_D5.0mm_W2.5mm_P5.00mm
J1: P2 femea; PinHeader_1x02_P2.54mm_Vertical
L1: 4t 20AWG 7mm; L_Axial_L5.3mm_D2.2mm_P7.62mm_Horizontal_Vishay_IM-1
Q1: PN2222A (BF494); TO-92_Inline_Wide
R1: 10k; R_Axial_DIN0207_L6.3mm_D2.5mm_P10.16mm_Horizontal
R2: 8k2; R_Axial_DIN0207_L6.3mm_D2.5mm_P10.16mm_Horizontal
R3: 5k6; R_Axial_DIN0207_L6.3mm_D2.5mm_P10.16mm_Horizontal
R4: 47; R_Axial_DIN0207_L6.3mm_D2.5mm_P10.16mm_Horizontal
R5: 1k; R_Axial_DIN0207_L6.3mm_D2.5mm_P10.16mm_Horizontal

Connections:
GND: BT1.2 (-), C1.1, C4.2, J1.2, R3.2, R4.2, R5.2
unnamed: AE1.1, C3.1, CV1.2, L1.2, Q1.1 (C)
unnamed: C2.1, R1.2, R5.1
unnamed: J1.1, R1.1
unnamed: C1.2, C2.2, Q1.3 (B), R2.2, R3.1
unnamed: C3.2, Q1.2 (E), R4.1
VCC: BT1.1 (+), C4.1, CV1.1, L1.1, R2.1

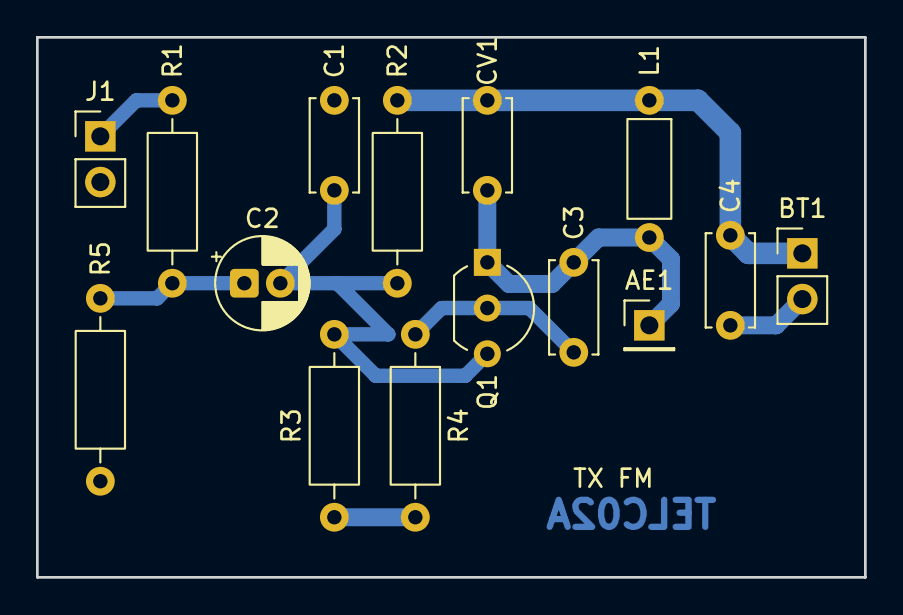
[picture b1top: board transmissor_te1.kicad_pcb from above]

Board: 2 copper layers, 46.0 x 30.0 mm, 15 parts (0 on the bottom side), 7 nets.
